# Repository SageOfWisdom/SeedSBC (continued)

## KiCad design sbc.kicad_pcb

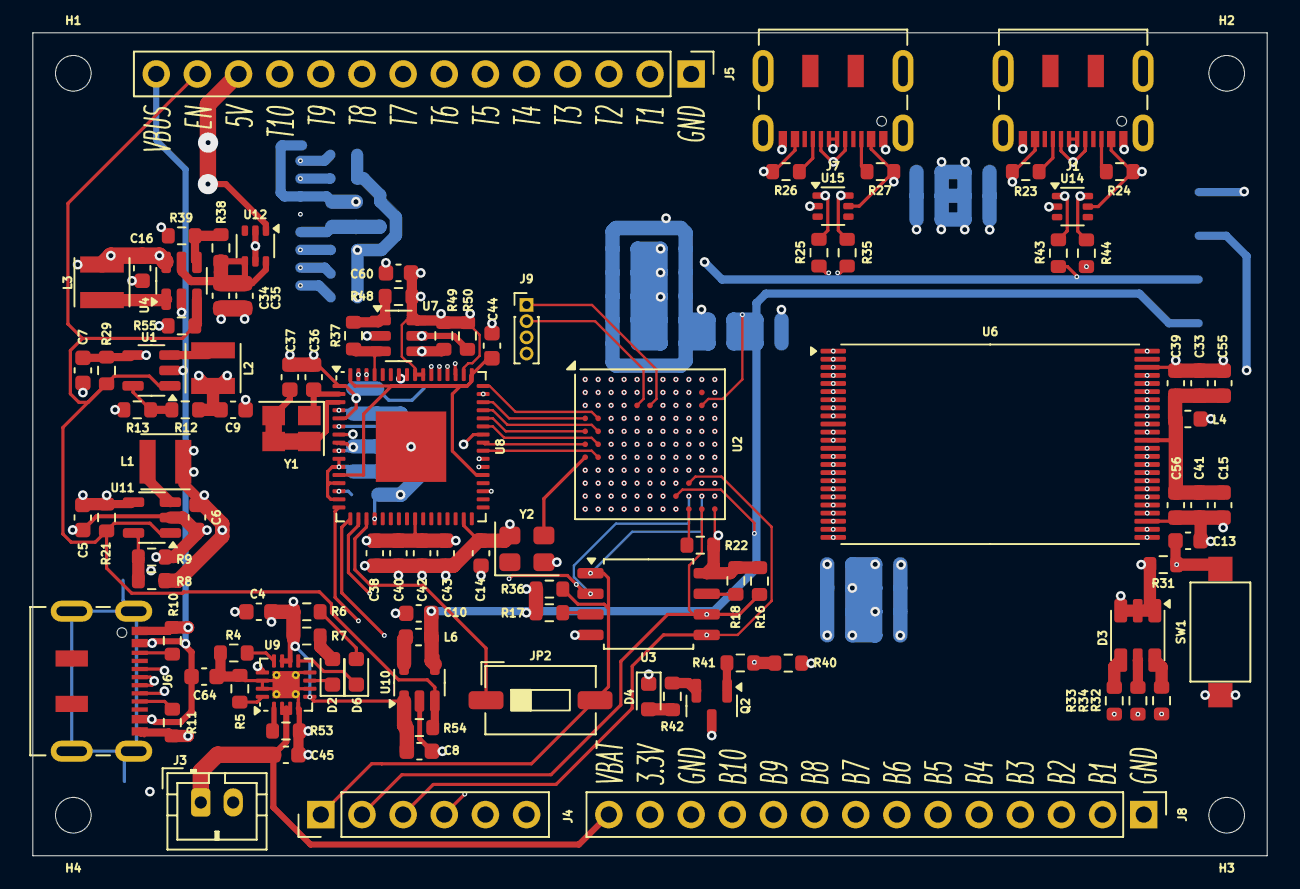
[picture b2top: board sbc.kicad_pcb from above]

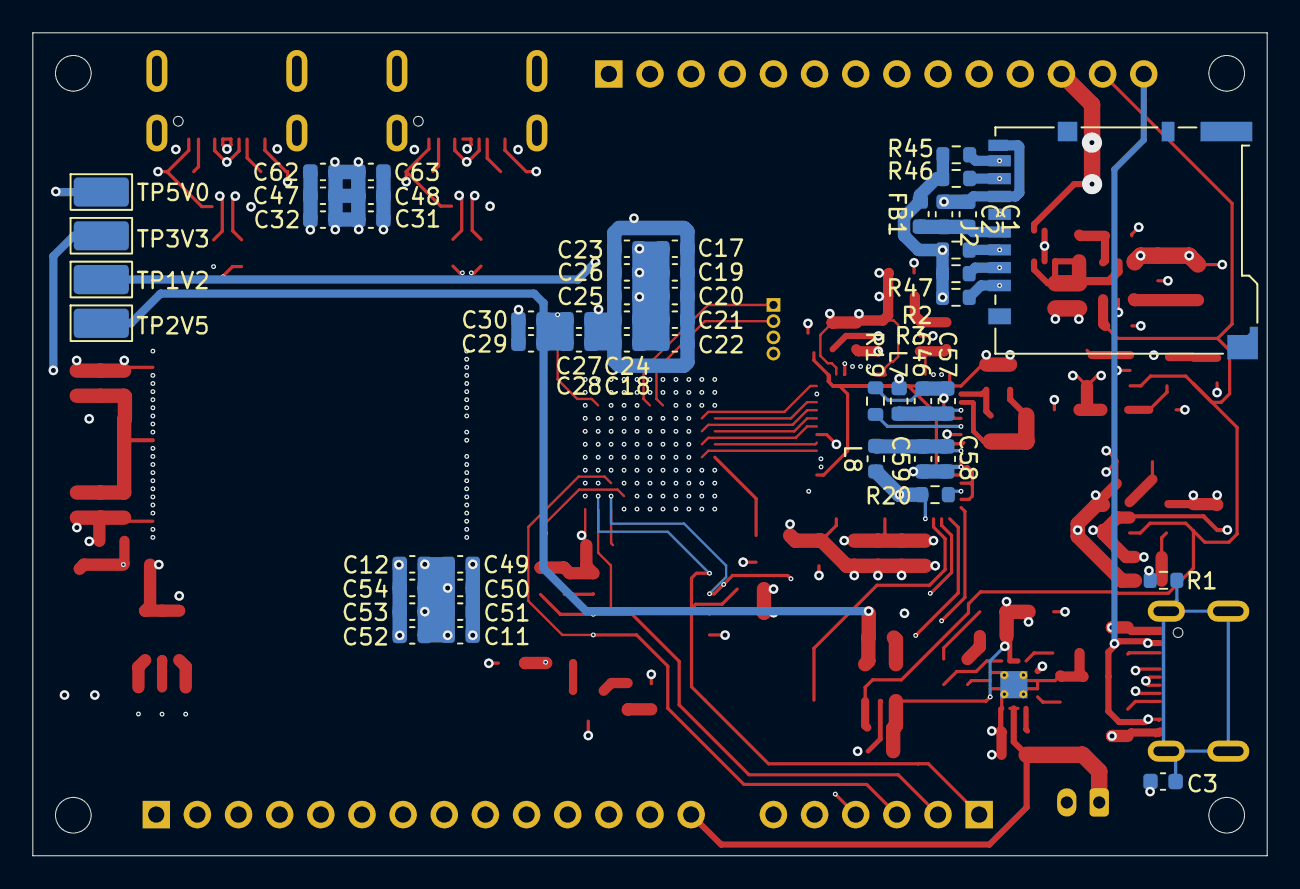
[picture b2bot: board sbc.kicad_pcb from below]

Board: 6 copper layers, 76.2 x 50.8 mm, 159 parts (51 on the bottom side), 158 nets.

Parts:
C1, C3, C11, C15, C17, C19, C20, C21, C22, C27, C28, C31, C32, C33, C49, C50, C51: 100nF; C_0603_1608Metric
C2, C6, C8, C9, C10, C16: 10uF; C_0603_1608Metric
C4, C5, C7, C13, C45, C46, C58: 4.7uF; C_0603_1608Metric
C12, C18, C23, C24, C25, C26, C29, C30, C47, C48, C52, C53, C54: 10nF; C_0603_1608Metric
C14: 0.01uF; C_0603_1608Metric
C34, C35: 22uF; C_0603_1608Metric
C36, C37: 27pF; C_0603_1608Metric
C38, C40, C42, C43, C60: 0.1uF; C_0603_1608Metric
C39, C41, C56, C64: 1uF; C_0603_1608Metric
C44: 3.3uF; C_0603_1608Metric
C55: 22nF; C_0603_1608Metric
C57, C59: 100n; C_0603_1608Metric
C62, C63: 2.2uF; C_0603_1608Metric
D2, D4, D6: LED; LED_0603_1608Metric
D3: SMLVN6RGB; LED_ROHM_SMLVN6
FB1: 600R; C_0603_1608Metric
H1, H2, H3, H4: MountingHole; MountingHole_2.2mm_M2
J1, J6, J7: USB_C_Receptacle_USB2.0_14P; USB_C_Receptacle_JAE_DX07S016JA1R1500
J2: Micro_SD_Card; microSD_HC_Hirose_DM3BT-DSF-PEJS
J3: Conn_01x02_Pin; JST_PH_B2B-PH-K_1x02_P2.00mm_Vertical
J4: Conn_01x06_Pin; PinHeader_1x06_P2.54mm_Vertical
J5, J8: Conn_01x14_Pin; PinHeader_1x14_P2.54mm_Vertical
J9: Conn_01x04_Pin; PinHeader_1x04_P1.00mm_Vertical
JP2: Jumper_2_Small_Open; SW_DIP_SPSTx01_Slide_6.7x4.1mm_W6.73mm_P2.54mm_LowProfile_J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
L1, L2, L3: 2.2uH; L_Neosid_SMS-ME3010
L4: 600R; L_0603_1608Metric
L6: 2.2uH; L_0603_1608Metric
L7, L8: 600; L_0603_1608Metric
Q2: BSS84; SOT-23
R1: 1M; R_0603_1608Metric
R2, R3, R6, R7, R20, R21, R22, R29, R31, R45, R46, R47, R48, R49, R50, R53, R54, R55: 10k; R_0603_1608Metric
R4: 2.94k; R_0603_1608Metric
R5: 4.32k; R_0603_1608Metric
R8: 450k; R_0603_1608Metric
R9, R12, R13: 100k; R_0603_1608Metric
R10, R11: 5.1k; R_0603_1608Metric
R16, R17, R18, R36: 4.7k; R_0603_1608Metric
R19: 12k; R_0603_1608Metric
R23, R24, R26, R27: 56k; R_0603_1608Metric
R25, R32, R33, R35, R43, R44: 20R; R_0603_1608Metric
R34: 60R; R_0603_1608Metric
R37, R40: 2.2k; R_0603_1608Metric
R38: 560k; R_0603_1608Metric
R39: 62k; R_0603_1608Metric
R41: 100R; R_0603_1608Metric
R42: 270R; R_0603_1608Metric
SW1: SW_Push; SW_SPST_CK_RS282G05A3
TP1V2, TP2V5, TP3V3, TP5V0: TestPoint_Flag; TestPoint_Keystone_5015_Micro_Mini
U1: TLV62568DBV; SOT-23-5
U2: a; BGA-121_9.0x9.0mm_Layout11x11_P0.8mm_Ball0.4mm_Pad0.35mm_NS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
U3: W25Q32JVSS; SOIC-8_5.3x5.3mm_P1.27mm
U4: TLV61070ADBV; SOT-23-6
U6: AS6C1616; TSOP-I-48_18.4x12mm_P0.5mm
U7: 93LCxxBxxOT; SOT-23-6
U8: FT2232HQ; QFN-64-1EP_9x9mm_P0.5mm_EP4.35x4.35mm
U9: BQ24230RGT; VQFN-16-1EP_3x3mm_P0.5mm_EP1.68x1.68mm_ThermalVias
U10: PAM2305AAB250; TSOT-23-5
U11: TLV62569DBV; SOT-23-5
U12: MIC94093YC6; SOT-363_SC-70-6
U14, U15: NUP2202; SOT-363_SC-70-6
Y1: 12MHz; Crystal_SMD_Abracon_ABM8AIG-4Pin_3.2x2.5mm
Y2: ASE-xxxMHz; Oscillator_SMD_Abracon_ASE-4Pin_3.2x2.5mm

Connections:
/FPGA + SRAM/CDONE: R40.1, R41.1, U2.K8 (CDONE)
/FPGA + SRAM/FIFO0: U2.H1 (IOL_18A), U8.38 (BDBUS0)
/FPGA + SRAM/FIFO1: U2.H2 (IOL_18B), U8.39 (BDBUS1)
/FPGA + SRAM/FIFO2: U2.G2 (IOL_14B), U8.40 (BDBUS2)
/FPGA + SRAM/FIFO3: U2.F1 (IOL_12A), U8.41 (BDBUS3)
/FPGA + SRAM/FIFO4: U2.F2 (IOL_12B), U8.43 (BDBUS4)
/FPGA + SRAM/FIFO5: U2.E1 (IOL_8A), U8.44 (BDBUS5)
/FPGA + SRAM/FIFO6: U2.E2 (IOL_10A), U8.45 (BDBUS6)
/FPGA + SRAM/FIFO7: U2.D1 (IOL_8B), U8.46 (BDBUS7)
/FPGA + SRAM/FIFO_RD_B: U2.J5 (IOB_78), U8.53 (BCBUS2)
/FPGA + SRAM/FIFO_RXF_B: U2.D2 (IOL_9A), U8.48 (BCBUS0)
/FPGA + SRAM/FIFO_TXE_B: U2.H3 (IOL_17B), U8.52 (BCBUS1)
/FPGA + SRAM/FIFO_WR_B: U2.J1 (IOL_23A), U8.54 (BCBUS3)
/FPGA + SRAM/FPGA/A0: U2.L7 (IOB_94), U6.25 (A0)
/FPGA + SRAM/FPGA/A1: U2.L8 (IOB_103_CBSEL0), U6.24 (A1)
/FPGA + SRAM/FPGA/A2: U2.K11 (IOR_115), U6.23 (A2)
/FPGA + SRAM/FPGA/A3: U2.J10 (IOR_117), U6.22 (A3)
/FPGA + SRAM/FPGA/A4: U2.J11 (IOR_114), U6.21 (A4)
/FPGA + SRAM/FPGA/A5: U2.H10 (IOR_116), U6.20 (A5)
/FPGA + SRAM/FPGA/A6: U2.H11 (IOR_119), U6.19 (A6)
/FPGA + SRAM/FPGA/A7: U2.G10 (IOR_120), U6.18 (A7)
/FPGA + SRAM/FPGA/A8: U2.C11 (IOR_160), U6.8 (A8)
/FPGA + SRAM/FPGA/A9: U2.C9 (IOT_172), U6.7 (A9)
/FPGA + SRAM/FPGA/A10: U2.B11 (IOR_161), U6.6 (A10)
/FPGA + SRAM/FPGA/A11: U2.B9 (IOT_174), U6.5 (A11)
/FPGA + SRAM/FPGA/A12: U2.A11 (IOT_168), U6.4 (A12)
/FPGA + SRAM/FPGA/A13: U2.A10 (IOT_170), U6.3 (A13)
/FPGA + SRAM/FPGA/A14: U2.A9 (IOT_178), U6.2 (A14)
/FPGA + SRAM/FPGA/A15: U2.A8 (IOT_190), U6.1 (A15)
/FPGA + SRAM/FPGA/A16: U2.A5 (IOT_207), U6.48 (A16)
/FPGA + SRAM/FPGA/A17: U2.G11 (IOR_129), U6.17 (A17)
/FPGA + SRAM/FPGA/A18: U2.F10 (IOR_136), U6.16 (A18)
/FPGA + SRAM/FPGA/A19: U2.D10 (IOR_154), U6.9 (A19)
/FPGA + SRAM/FPGA/CRESET_B: R22.1, U2.L9 (~CRESET)
/FPGA + SRAM/FPGA/DQ0: U2.J8 (IOB_91), U6.29 (DQ0)
/FPGA + SRAM/FPGA/DQ1: U2.H9 (IOB_104_CBSEL1), U6.31 (DQ1)
/FPGA + SRAM/FPGA/DQ2: U2.G9 (IOR_128), U6.33 (DQ2)
/FPGA + SRAM/FPGA/DQ3: U2.E8 (IOR_146), U6.35 (DQ3)
/FPGA + SRAM/FPGA/DQ4: U2.D9 (IOR_147), U6.38 (DQ4)
/FPGA + SRAM/FPGA/DQ5: U2.C8 (IOT_179), U6.40 (DQ5)
/FPGA + SRAM/FPGA/DQ6: U2.B8 (IOT_177), U6.42 (DQ6)
/FPGA + SRAM/FPGA/DQ7: U2.A7 (IOT_192), U6.44 (DQ7)
/FPGA + SRAM/FPGA/DQ8: U2.H7 (IOB_87), U6.30 (DQ8)
/FPGA + SRAM/FPGA/DQ9: U2.G8 (IOR_118), U6.32 (DQ9)
/FPGA + SRAM/FPGA/DQ10: U2.F9 (IOR_137), U6.34 (DQ10)
/FPGA + SRAM/FPGA/DQ11: U2.E9 (IOR_144), U6.36 (DQ11)
/FPGA + SRAM/FPGA/DQ12: U2.D7 (IOT_181), U6.39 (DQ12)
/FPGA + SRAM/FPGA/DQ13: U2.C7 (IOT_191), U6.41 (DQ13)
/FPGA + SRAM/FPGA/DQ14: U2.B7 (IOT_197_GBIN1), U6.43 (DQ14)
/FPGA + SRAM/FPGA/DQ15: U2.A6 (IOT_206), U6.45 (DQ15)
/FPGA + SRAM/FPGA/SPI_CNFG_CS: J4.1, JP2.2 (B), R36.1, U2.K10 (IOB_108_SS), U3.1 (~CS)
/FPGA + SRAM/FPGA/SPI_CNFG_DI: J4.3, U2.J9 (IOB_106_SDI), U3.5 (DI/IO_{0}), U8.17 (ADBUS1)
/FPGA + SRAM/FPGA/SPI_CNFG_DO: J4.4, U2.K9 (IOB_105_SDO), U3.2 (DO/IO_{1}), U8.18 (ADBUS2)
/FPGA + SRAM/FPGA/SPI_CNFG_SCK: J4.2, R16.1, U2.L10 (IOB_107_SCK), U3.6 (CLK), U8.16 (ADBUS0)
/FPGA + SRAM/FPGA/SRAM_CE2: U2.E11 (IOR_148), U6.12 (CE2)
/FPGA + SRAM/FPGA/SRAM_CE_B: U2.K7 (IOB_89), U6.26 (CE#)
/FPGA + SRAM/FPGA/SRAM_LB_B: U2.F11 (IOR_140_GBIN3), U6.15 (LB#)
/FPGA + SRAM/FPGA/SRAM_OE_B: U2.J7 (IOB_86), U6.28 (OE#)
/FPGA + SRAM/FPGA/SRAM_UB_B: U2.E10 (IOR_141_GBIN2), U6.14 (UB#)
/FPGA + SRAM/FPGA/SRAM_WE_B: U2.D11 (IOR_152), U6.11 (WE#)
/FPGA + SRAM/IO_B1: J8.2, U2.K6 (IOB_82_GBIN4)
/FPGA + SRAM/IO_B2: J8.3, U2.K5 (IOB_79)
/FPGA + SRAM/IO_B3: J8.4, U2.L5 (IOB_81_GBIN5)
/FPGA + SRAM/IO_B4: J8.5, U2.K4 (IOB_73)
/FPGA + SRAM/IO_B5: J8.6, U2.L4 (IOB_72)
/FPGA + SRAM/IO_B6: J8.7, U2.K3 (IOB_63)
/FPGA + SRAM/IO_B7: J8.8, U2.L3 (IOB_71)
/FPGA + SRAM/IO_B8: J8.9, U2.K2 (IOL_25A)
/FPGA + SRAM/IO_B9: J8.10, U2.L2 (IOB_61)
/FPGA + SRAM/IO_B10: J8.11, U2.L1 (IOB_56)
/FPGA + SRAM/IO_T1: J5.2, U2.B6 (IOT_198_GBIN0)
/FPGA + SRAM/IO_T2: J5.3, U2.B5 (IOT_208)
/FPGA + SRAM/IO_T3: J5.4, U2.A4 (IOT_211)
/FPGA + SRAM/IO_T4: J5.5, U2.B4 (IOT_219)
/FPGA + SRAM/IO_T5: J5.6, U2.A3 (IOT_223)
/FPGA + SRAM/IO_T6: J5.7, U2.B3 (IOT_221)
/FPGA + SRAM/IO_T7: J5.8, U2.A2 (IOT_222)
/FPGA + SRAM/IO_T8: J5.9, U2.C2 (IOL_5A)
/FPGA + SRAM/IO_T9: J5.10, U2.A1 (IOT_225)
/FPGA + SRAM/IO_T10: J5.11, U2.C1 (IOL_5B)
/FPGA + SRAM/LED_B: R32.1, U2.K1 (IOL_23B)
/FPGA + SRAM/LED_G: R33.1, U2.J3 (IOB_57)
/FPGA + SRAM/LED_R: R34.1, U2.J2 (IOL_25B)
/FPGA + SRAM/SD_CLK: J2.5 (CLK), U2.E3 (IOL_10B)
/FPGA + SRAM/SD_DAT0: J2.7 (DAT0), R46.2, U2.D3 (IOL_9B)
/FPGA + SRAM/SD_DAT1: J2.8 (DAT1), R45.2, U2.D5 (IOT_212)
/FPGA + SRAM/SD_DAT2: J2.1 (DAT2), R3.2, U2.G3 (IOL_17A)
/FPGA + SRAM/SD_DAT3: J2.2 (DAT3/CD), R2.2, U2.F3 (IOL_13B_GBIN7)
/FPGA + SRAM/SPI_CNFG_CS_B: JP2.1 (A), U8.19 (ADBUS3)
/FPGA + SRAM/SRAM/VCC: C15.1, C33.1, C39.1, C41.1, C55.1, C56.1, L4.2, U6.37 (VCC)
/FPGA + SRAM/USB2_DN: R25.2, U2.B1 (IOL_2A)
/FPGA + SRAM/USB2_DP: R35.2, U2.B2 (IOL_2B)
/FPGA + SRAM/USB3_DN: R43.2, U2.C4 (IOL_4A)
/FPGA + SRAM/USB3_DP: R44.2, U2.C3 (IOL_4B)
/FPGA + SRAM/USR_BTN1: C13.1, R31.1, SW1.2, U2.J4 (IOB_64)
/SD MMC/3.3V: C1.1, C2.1, FB1.1, J2.4 (VDD)
/SD MMC/SD_CMD: J2.3 (CMD), R47.2, U2.F4 (IOL_13A)
/USB/1.8V: C44.1, U8.12 (VCORE), U8.37 (VCORE), U8.49 (VREGOUT), U8.64 (VCORE)
/USB/D1+: J6.A6 (D+), J6.B6 (D+), U8.8 (DP)
/USB/D1-: J6.A7 (D-), J6.B7 (D-), U8.7 (DM)
/USB/D2+: J7.A6 (D+), J7.B6 (D+), R35.1, U15.6
/USB/D2-: J7.A7 (D-), J7.B7 (D-), R25.1, U15.1
/USB/D3+: J1.A6 (D+), J1.B6 (D+), R44.1, U14.6
/USB/D3-: J1.A7 (D-), J1.B7 (D-), R43.1, U14.1
CLK: U2.G1 (IOL_14A_GBIN6), Y2.3 (OUT)
EN: J5.13, R21.1, R29.1, R54.2, R55.2, U1.1 (EN), U4.3 (EN), U10.3 (EN), U11.1 (EN)
EXT_PLL1N: J9.4, U2.L6 (GNDPLL0)
EXT_PLL1P: J9.3, U2.J6 (VCCPLL0)
EXT_PLL2N: J9.2, U2.C5 (GNDPLL1)
EXT_PLL2P: J9.1, U2.C6 (VCCPLL1)
GND: C1.2, C2.2, C3.2, C4.2, C5.2, C6.2, C7.2, C8.2, C9.2, C10.2, C11.2, C12.2, C13.2, C14.2, C15.2, C16.2, C17.2, C18.2, C19.2, C20.2, C21.2, C22.2, C23.2, C24.2, C25.2, C26.2, C27.2, C28.2, C29.2, C30.2, C31.2, C32.2, C33.2, C34.2, C35.2, C36.2, C37.2, C38.2, C39.2, C40.2, C41.2, C42.2, C43.2, C44.2, C45.2, C46.2, C47.2, C48.2, C49.2, C50.2, C51.2, C52.2, C53.2, C54.2, C55.2, C56.2, C57.2, C58.2, C59.2, C60.2, C62.2, C63.2, C64.2, D4.1 (K), J1.A1 (GND), J1.A12 (GND), J1.B1 (GND), J1.B12 (GND), J1.S1 (SHIELD), J2.6 (VSS), J2.9 (SHIELD), J3.2, J4.6, J5.1, J6.A1 (GND), J6.A12 (GND), J6.B1 (GND), J6.B12 (GND), J7.A1 (GND), J7.A12 (GND), J7.B1 (GND), J7.B12 (GND), J7.S1 (SHIELD), J8.1, J8.12, R1.2, R4.2, R5.2, R9.1, R10.2, R11.2, R13.1, R19.1, R39.1, R53.2, SW1.1, U1.2 (GND), U2.E5 (GND), U2.E6 (GND), U2.E7 (GND), U2.F5 (GND), U2.F6 (GND), U2.F7 (GND), U2.G5 (GND), U2.G6 (GND), U2.G7 (GND), U2.H5 (GND), U3.4 (GND), U4.2 (GND), U6.27 (VSS), U6.46 (VSS), U7.2 (GND), U8.1 (GND), U8.5 (GND), U8.10 (AGND), U8.11 (GND), U8.13 (TEST), U8.15 (GND), U8.25 (GND), U8.35 (GND), U8.47 (GND), U8.51 (GND), U8.65 (GND), U9.4 (CE), U9.6 (EN1), U9.8 (VSS), U9.14 (TMR), U9.15 (TD), U9.17 (VSS), U10.2 (GND), U11.2 (GND), U12.2 (GND), U12.5 (GND), U14.2, U15.2, Y2.2 (GND)
unnamed: D2.2 (A), R7.1
unnamed: D2.1 (K), U9.7 (PGOOD)
unnamed: D3.6 (BK), R32.2
unnamed: D3.4 (GK), R33.2
unnamed: D3.5 (RK), R34.2
unnamed: D4.2 (A), R42.1
unnamed: D6.2 (A), R6.1
unnamed: D6.1 (K), U9.9 (CHG)
unnamed: J1.A5 (CC1), R24.1
unnamed: J1.B5 (CC2), R23.1
unnamed: J6.A5 (CC1), R10.1
unnamed: J6.B5 (CC2), R11.1
unnamed: C3.1, J6.S1 (SHIELD), R1.1
unnamed: J7.A5 (CC1), R27.1
unnamed: J7.B5 (CC2), R26.1
unnamed: Q2.1 (G), R41.2
unnamed: Q2.2 (S), R42.2
unnamed: R12.1, R13.2, U1.5 (FB)
unnamed: L2.1, U1.3 (SW)
unnamed: R18.1, U3.7 (~HOLD/~RESET/IO_{3})
unnamed: R17.1, U3.3 (~WP/IO_{2})
unnamed: L3.2, U4.1 (SW)
unnamed: R38.1, R39.2, U4.4 (V_{FB})
unnamed: R49.1, U7.4 (CLK), U8.62 (EECLK)
unnamed: R50.1, U7.5 (CS), U8.63 (EECS)
unnamed: R37.2, U7.3 (DI), U8.61 (EEDATA)
unnamed: R37.1, R48.1, U7.1 (DO)
unnamed: C36.1, U8.2 (OSCI), Y1.1
unnamed: C37.1, U8.3 (OSCO), Y1.2, Y1.3, Y1.4
unnamed: R19.2, U8.6 (REF)
unnamed: C46.1, C57.1, L7.2, U8.4 (VPHY)
unnamed: C58.1, C59.1, L8.2, U8.9 (VPLL)
unnamed: R20.2, U8.14 (~RESET)
unnamed: R4.1, U9.12 (ILIM)
unnamed: R5.1, U9.16 (ISET)
unnamed: R53.1, U9.1 (TS)
unnamed: L6.1, U10.5 (SW)
unnamed: R8.1, R9.2, U11.5 (FB)
unnamed: L1.1, U11.3 (SW)
P1V2: C9.1, C17.1, C18.1, C19.1, C20.1, C21.1, C22.1, C23.1, C24.1, C25.1, C26.1, L2.2, R12.2, TP1V2.1, U2.D4 (VCC), U2.D8 (VCC), U2.H4 (VCC), U2.H8 (VCC)
P2V5: C10.1, C27.1, C28.1, C29.1, C30.1, L6.2, TP2V5.1, U2.C10 (VPP_2V5), U10.4 (FB)
P3V3: C6.1, C11.1, C12.1, C14.1, C38.1, C40.1, C42.1, C43.1, C49.1, C50.1, C51.1, C52.1, C53.1, C54.1, C60.1, D3.1 (BA), D3.2 (RA), D3.3 (GA), FB1.2, J4.5, J8.13, L1.2, L4.1, L7.1, L8.1, Q2.3 (D), R2.1, R3.1, R8.2, R16.2, R17.2, R18.2, R20.1, R22.2, R31.2, R36.2, R40.2, R45.1, R46.1, R47.1, R48.2, R49.2, R50.2, TP3V3.1, U2.D6 (VCCIO_0), U2.E4 (VCCIO_3), U2.F8 (VCCIO_1), U2.G4 (VCCIO_3), U2.H6 (VCCIO_2), U2.L11 (VCC_SPI), U3.8 (VCC), U7.6 (VCC), U8.20 (VCCIO), U8.31 (VCCIO), U8.42 (VCCIO), U8.50 (VREGIN), U8.55 (BCBUS4), U8.56 (VCCIO), Y2.4 (Vdd)
P5V: C34.1, C35.1, R38.2, U4.5 (V_{OUT}), U12.4 (IN), U12.6 (EN)
USB_VBUS: C64.1, J5.14, J6.A4 (VBUS), J6.A9 (VBUS), J6.B4 (VBUS), J6.B9 (VBUS), U9.13 (IN)
USB_VBUS2: C31.1, C32.1, C47.1, C48.1, C62.1, C63.1, J1.A4 (VBUS), J1.A9 (VBUS), J1.B4 (VBUS), J1.B9 (VBUS), J5.12, J7.A4 (VBUS), J7.A9 (VBUS), J7.B4 (VBUS), J7.B9 (VBUS), R23.2, R24.2, R26.2, R27.2, TP5V0.1, U12.1 (OUT), U14.5, U15.5
V_BAT: C45.1, J3.1, J8.14, U9.2 (BAT), U9.3 (BAT)
V_SYS: C4.1, C5.1, C7.1, C8.1, C16.1, L3.1, R6.2, R7.2, R21.2, R29.2, R54.1, R55.1, U1.4 (VIN), U4.6 (V_{IN}), U9.5 (EN2), U9.10 (OUT), U9.11 (OUT), U10.1 (Vin), U11.4 (VIN)

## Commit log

2025-10-09 setting up repository
2025-10-09 added functional unit hierarchy
2025-10-09 Changed power regulators, filled out DRAM, begin changing FPGA from ECP5 to ICE40
2025-10-09 Saving before changing RAM from DDR3 to Parallel SDR SRAM
2025-10-09 Added more I/O. Changed power regulators
2025-10-09 Power routed. Saving before reworking ICE40 pins to optimize layout
2025-10-10 Finished board. Added BOM
2025-10-13 End of Version 1.0. Feedback received
2025-10-13 Started rev1.1. Added revision file hierarchy
2025-10-27 started new through-hole only version
2025-11-22 Finished revision 2.0 modifications and layout. Added ReadMe
2025-11-22 Fixed ReadMe. Fixed PCB Silkscreen
